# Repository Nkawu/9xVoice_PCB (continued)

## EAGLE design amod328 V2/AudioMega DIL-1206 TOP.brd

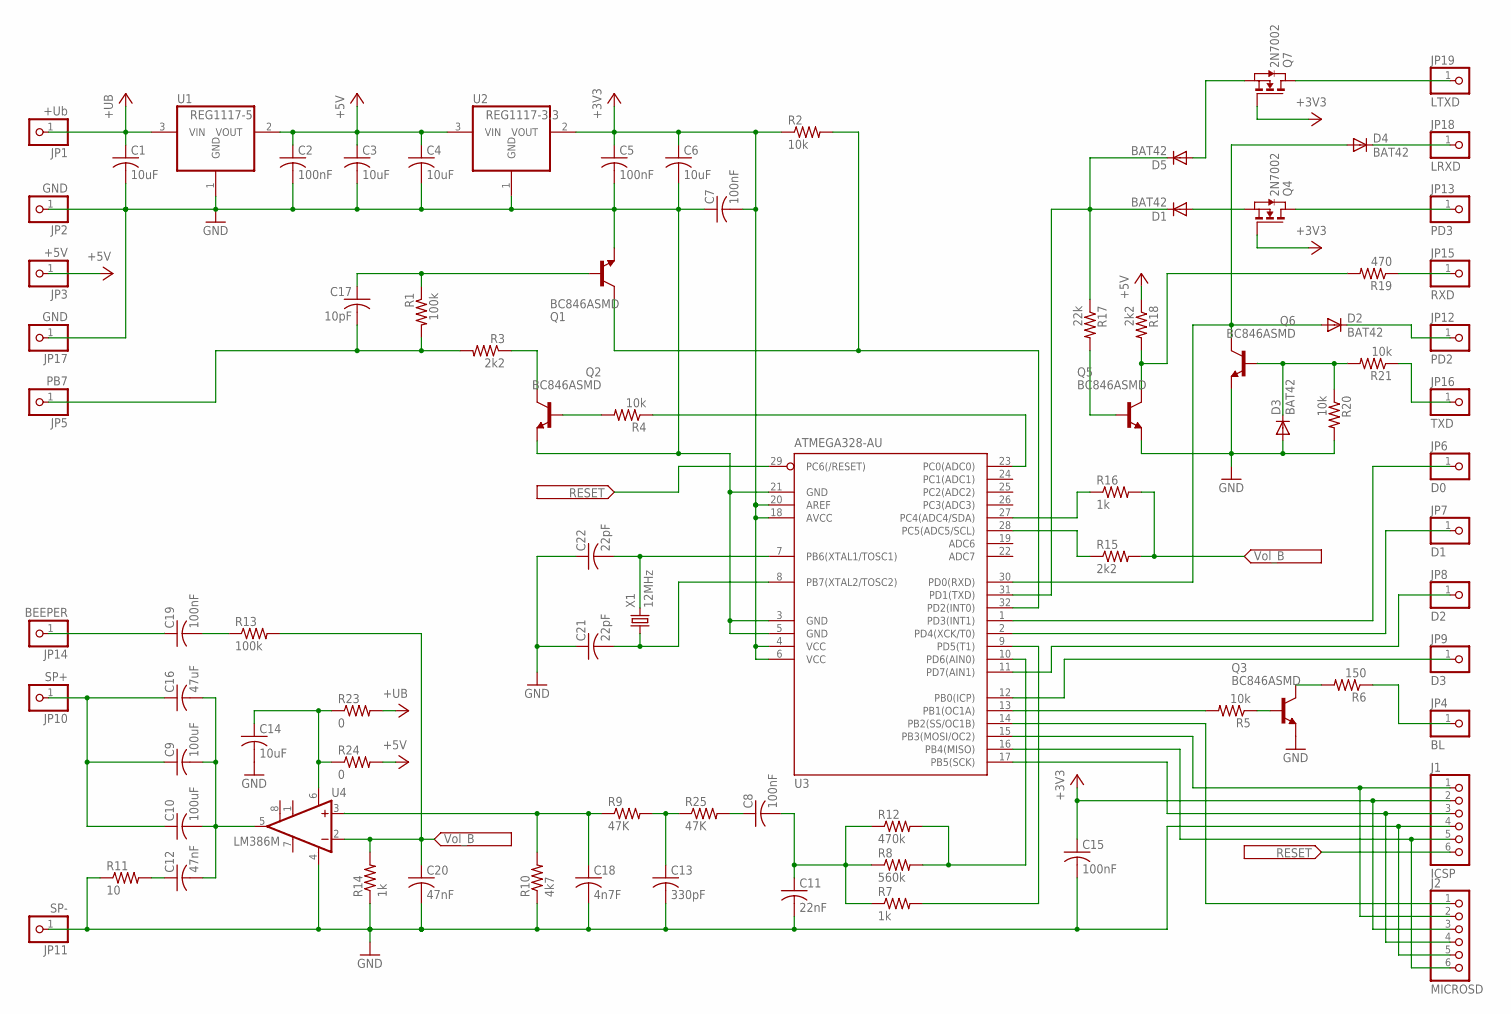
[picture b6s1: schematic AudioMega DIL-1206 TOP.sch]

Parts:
C1, C3, C4, C6, C14: 10uF; C1206
C2, C5, C7, C8, C15, C19: 100nF; C1206
C9, C10: 100uF; C1206
C11: 22nF; C1206
C12, C20: 47nF; C1206
C13: 330pF; C1206
C16: 47uF; C1206
C17: 10pF; C1206
C18: 4n7F; C1206
C21, C22: 22pF; C1206
D1, D2, D3, D4, D5: BAT42; SOD123
J1: ICSP; 1X06
J2: MICROSD; 1X06
JP1: +Ub; 1X01
JP2, JP17: GND; 1X01
JP3: +5V; 1X01
JP4: BL; 1X01
JP5: PB7; 1X01
JP6: D0; 1X01
JP7: D1; 1X01
JP8: D2; 1X01
JP9: D3; 1X01
JP10: SP+; 1X01
JP11: SP-; 1X01
JP12: PD2; 1X01
JP13: PD3; 1X01
JP14: BEEPER; 1X01
JP15: RXD; 1X01
JP16: TXD; 1X01
JP18: LRXD; 1X01
JP19: LTXD; 1X01
Q1, Q2, Q3, Q5, Q6: BC846ASMD; SOT23
Q4, Q7: 2N7002; SOT-23
R1, R13: 100k; R1206
R2, R4, R5, R20, R21: 10k; R1206
R3, R15, R18: 2k2; R1206
R6: 150; R1206
R7, R14, R16: 1k; R1206
R8: 560k; R1206
R9, R25: 47K; R1206
R10: 4k7; R1206
R11: 10; R1206
R12: 470k; R1206
R17: 22k; R1206
R19: 470; R1206
R23, R24: 0; R1206
U1: REG1117-5; SOT223
U2: REG1117-3.3; SOT223
U3: ATMEGA328-AU; TQFP32-08
U4: LM386M; SO08
X1: 12MHz; HC49US

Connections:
+3V3: C5.1, C6.1, C7.2, C15.1, J1.2, J2.3, Q4.3 (G), Q7.3 (G), R2.1, U2.2 (VOUT), U3.4 (VCC), U3.6 (VCC), U3.18 (AVCC), U3.20 (AREF)
+5V: C2.1, C3.1, C4.1, JP3.1, R18.1, R24.2, U1.2 (VOUT), U2.3 (VIN)
+UB: C1.1, JP1.1, R23.2, U1.3 (VIN)
B7: C17.2, JP5.1, R1.2, R3.2
BACKLIGHT: JP4.1, R6.1
BEEPER: C19.1, JP14.1
CLK: Q1.3 (C), R2.2, U3.32 (PD2(INT0))
D0: JP6.1, U3.1 (PD3(INT1))
D1: JP7.1, U3.2 (PD4(XCK/T0))
D2: JP8.1, U3.11 (PD7(AIN1))
D3: JP9.1, U3.12 (PB0(ICP))
GND: C1.2, C2.2, C3.2, C4.2, C5.2, C6.2, C7.1, C11.2, C13.2, C14.2, C15.2, C18.2, C20.2, C21.1, C22.1, D3.A, J1.4, J2.5, JP2.1, JP11.1, JP17.1, Q1.2 (E), Q2.2 (E), Q3.2 (E), Q5.2 (E), Q6.2 (E), R10.1, R11.1, R14.1, R20.2, U1.1 (GND), U2.1 (GND), U3.3 (GND), U3.5 (GND), U3.21 (GND), U4.4 (GND)
MISO: J1.5, J2.6, U3.16 (PB4(MISO))
MOSI: J1.1, J2.2, U3.15 (PB3(MOSI/OC2))
unnamed: R4.1, U3.23 (PC0(ADC0))
unnamed: C8.1, R25.2
unnamed: D4.C, JP18.1
unnamed: JP19.1, Q7.1 (D)
unnamed: D5.A, Q7.2 (S)
unnamed: C22.2, U3.7 (PB6(XTAL1/TOSC1)), X1.2
unnamed: C21.2, U3.8 (PB7(XTAL2/TOSC2)), X1.1
unnamed: Q2.1 (B), R4.2
unnamed: R16.1, U3.27 (PC4(ADC4/SDA))
unnamed: R15.1, U3.28 (PC5(ADC5/SCL))
unnamed: Q2.3 (C), R3.1
unnamed: C17.1, Q1.1 (B), R1.1
unnamed: C12.1, R11.2
unnamed: C9.2, C10.2, C12.2, C16.2, U4.5 (OUT)
unnamed: C18.1, R9.1, R10.2, U4.3 (+IN)
unnamed: C19.2, R13.1
unnamed: C14.1, R23.1, R24.1, U4.6 (VS)
unnamed: C13.1, R9.2, R25.1
unnamed: C8.2, C11.1, R7.1, R8.1, R12.1
unnamed: Q3.3 (C), R6.2
unnamed: R7.2, U3.9 (PD5(T1))
unnamed: R8.2, R12.2, U3.10 (PD6(AIN0))
unnamed: Q3.1 (B), R5.1
unnamed: R5.2, U3.13 (PB1(OC1A))
unnamed: D3.C, Q6.1 (B), R20.1, R21.2
unnamed: D2.A, D4.A, Q6.3 (C), U3.30 (PD0(RXD))
unnamed: Q5.3 (C), R18.2, R19.2
unnamed: Q5.1 (B), R17.2
unnamed: D1.A, Q4.2 (S)
unnamed: D1.C, D5.C, R17.1, U3.31 (PD1(TXD))
PB2: J2.1, U3.14 (PB2(SS/OC1B))
PD2: D2.C, JP12.1
PD3: JP13.1, Q4.1 (D)
RESET: J1.6, U3.29 (PC6(/RESET))
RXD: JP15.1, R19.1
SCK: J1.3, J2.4, U3.17 (PB5(SCK))
SPEAKER+: C9.1, C10.1, C16.1, JP10.1
TXD: JP16.1, R21.1
VOL_B: C20.1, R13.2, R14.2, R15.2, R16.2, U4.2 (-IN)

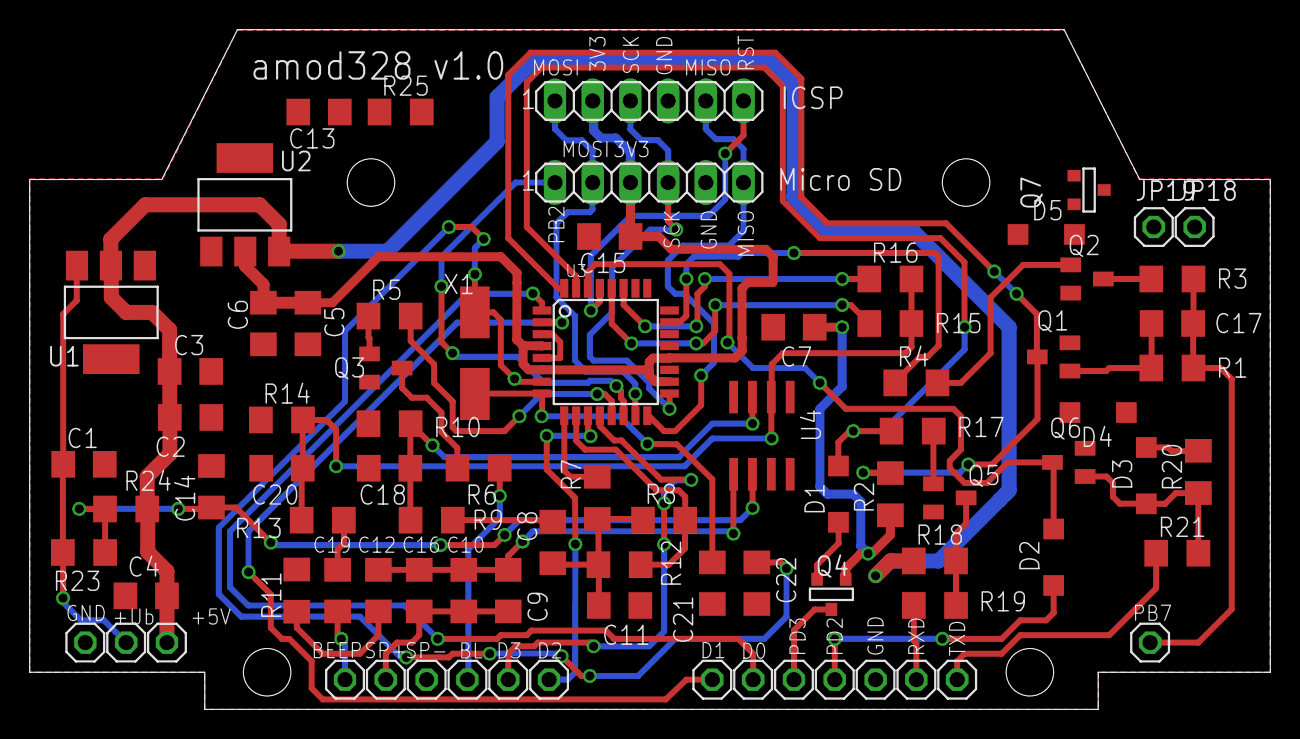
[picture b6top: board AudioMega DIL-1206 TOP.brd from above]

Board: 2 copper layers, 83.6 x 45.8 mm, 84 parts (0 on the bottom side), 53 nets.

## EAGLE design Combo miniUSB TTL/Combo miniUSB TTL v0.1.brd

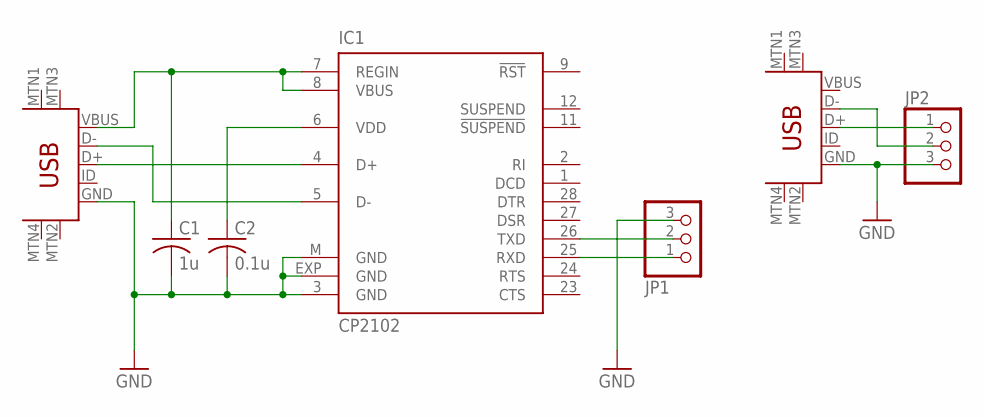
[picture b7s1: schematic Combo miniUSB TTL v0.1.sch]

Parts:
C1: 1u; C0805
C2: 0.1u; C0805
IC1: CP2102; MLP28
JP1, JP2: PINHD-1X3; 1X03
X1, X2: USB-MINIB-5PIN; USB-MINIB

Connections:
D+: IC1.4 (D+), X2.D+
D-: IC1.5 (D-), X2.D-
GND: C1.2, C2.2, IC1.3 (GND), IC1.EXP (GND), IC1.M (GND), JP1.3, JP2.3, X1.GND, X2.GND
unnamed: JP2.1, X1.D+
unnamed: JP2.2, X1.D-
unnamed: C2.1, IC1.6 (VDD)
RXD: IC1.25 (RXD), JP1.1
TXD: IC1.26 (TXD), JP1.2
VBUS: C1.1, IC1.7 (REGIN), IC1.8 (VBUS), X2.VBUS

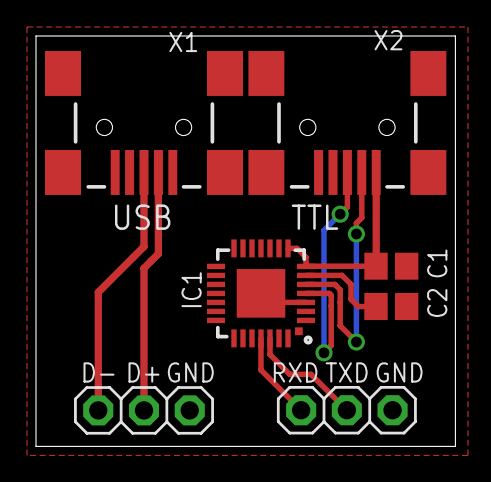
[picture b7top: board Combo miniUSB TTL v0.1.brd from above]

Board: 2 copper layers, 23.3 x 22.8 mm, 7 parts (0 on the bottom side), 9 nets.

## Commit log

2018-08-31 Initial add
2018-08-31 Add HaGeHa Original
